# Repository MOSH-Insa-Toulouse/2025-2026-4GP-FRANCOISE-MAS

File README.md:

# Capteur de déformation en graphite - Projet 4GP

  > **Génie Physique - INSA Toulouse - Promotion 2025-2026**
  > UF « Du capteur au banc de test »

  ## Sommaire
  - [Présentation générale](#présentation-générale)
  - [1. Le capteur graphite](#1-le-capteur-graphite)
    - [1.1 Principe physique](#11-principe-physique)
    - [1.2 Objectifs et livrables](#12-objectifs-et-livrables)
    - [1.3 Matériel](#13-matériel)
  - [2. Conditionnement du signal](#2-conditionnement-du-signal)
    - [2.1 Étage transimpédance (LTSpice)](#21-étage-transimpédance-ltspice)
    - [2.2 Modèle mathématique](#22-modèle-mathématique)
  - [3. Carte électronique (shield Arduino)](#3-carte-électronique-shield-arduino)
    - [3.1 Routage sous KiCad](#31-routage-sous-kicad)
    - [3.2 Fabrication et brochage](#32-fabrication-et-brochage)
  - [4. Logiciel embarqué](#4-logiciel-embarqué)
  - [5. Application mobile](#5-application-mobile)
  - [6. Banc de caractérisation](#6-banc-de-caractérisation)
  - [7. Résultats et analyse](#7-résultats-et-analyse)
  - [8. Bilan et perspectives](#8-bilan-et-perspectives)
  - [Remerciements](#remerciements)
  - [Contacts](#contacts)

  ---

  ## Présentation générale

  Ce projet propose une chaîne de mesure complète - acquisition, traitement, affichage et
  archivage des résultats - construite autour d'un capteur de déformation **low-tech** : une simple piste
  de graphite tracée au crayon sur du papier.

  L'ensemble s'appuie sur l'article de **Lin, C.-W., Zhao, Z., Kim, J. et al. (2014)**,
  *« Pencil Drawn Strain Gauges and Chemiresistors on Paper »* (Nature). L'article de
  référence est disponible dans le dépôt.

  On cherche ic à faire un dispositif **bon marché,
  reproductible, réparable et fabricable avec des moyens d'atelier ordinaires**, tout en
  restant exploitable scientifiquement.

  ---

  ## 1. Le capteur graphite

  ### 1.1 Principe physique

  Le capteur est obtenu en frottant un crayon sur une feuille de papier (≈ 0,35 mm
  d'épaisseur). Le graphite s'accroche aux fibres et forme un réseau granulaire : le
  courant circule par les contacts entre grains et par effet tunnel entre particules
  voisines. La résistance du tracé dépend donc directement de la distance entre grains.

  Lorsque le papier est plié, cette distance évolue :

  | Sollicitation | Effet sur le réseau | Résistance |
  |---------------|---------------------|------------|
  | **Traction**  | Les grains s'écartent | **augmente** |
  | **Compression** | Les grains se rapprochent | **diminue** |

  La sensibilité dépend de plusieurs facteurs : dureté de la mine, quantité de graphite
  déposée, géométrie du tracé, humidité et température ambiantes. Différentes duretés ont
  été testées (2H, HB, B, 3B, 4B, 6B) afin de comparer leur comportement.

  ### 1.2 Objectifs et livrables

  L'objectif est de remonter à l'angle de flexion (donc à la déformation) à partir de la
  seule mesure de résistance. Le travail se décompose en cinq étapes : simulation du
  conditionnement analogique, conception du PCB, programmation du microcontrôleur,
  développement de l'application mobile et caractérisation expérimentale.

  Livrables produits :
  - un **shield Arduino** regroupant l'électronique de mesure, d'amplification et de
    communication.
  - un **code Arduino (C++)** organisé en pseudo machine à états (car nous avons essayer mais ce n'est pas réellement une machine à état).
  - une **IHM (interface human machine) en format .py** de supervision et de tracé temps réel.
  - une **datasheet** récapitulant la caractérisation du capteur.

  ### 1.3 Matériel

  **Électronique**
  - Arduino UNO Rev 3
  - Amplificateur opérationnel LTC1050
  - Potentiomètre numérique SPI MCP41010 (10 kΩ, 256 pas)
  - Écran OLED 0,96" SSD1306 (I²C)
  - Encodeur rotatif KY-040
  - Module Bluetooth HC-05
  - Passifs : résistances (2×1 kΩ, 1×10 kΩ, 2×100 kΩ) et condensateurs (2×100 nF, 1×1 µF)
  - Pour comparaison : capteur de flexion commercial (Flex Sensor) + résistance de charge 47 kΩ

  **Fabrication du capteur**
  - Papier souple, crayons de duretés variées, contacts et pinces de test Mueller

  **Logiciels**
  - LTSpice (simulation) · KiCad (PCB) · Arduino IDE (firmware)

  **Banc d'essai**
  - module imprimé en 3D à rayons de courbure étalonnés + instrumentation de mesure. Nous avons réutilisé les système imprimés les années passées pour rester dans la démarche **low-tech**

  ---

  ## 2. Conditionnement du signal

  ### 2.1 Étage transimpédance (LTSpice)

  À vide, le capteur affiche une résistance très élevée (du MΩ au GΩ selon la mine).
  Sous 5 V, le courant traversant n'est que de l'ordre du nanoampère : il faut donc un
  étage d'amplification pour ramener le signal dans la plage 0–5 V de l'ADC de l'Arduino.

  Un montage **transimpédance** autour du LTC1050 a été simulé sous LTSpice afin de valider
  le gain, étudier la réponse en fréquence et dimensionner le filtrage. Trois filtres
  passe-bas améliorent le rapport signal/bruit :

  1. **Entrée (~175 Hz)** — atténue les vibrations et tremblements mécaniques ;
  2. **Rétroaction active (~1,6 Hz)** — coupe le bruit secteur 50 Hz ;
  3. **Sortie (~1,6 kHz)** — supprime les parasites haute fréquence de l'électronique
     numérique.

  <p align="center">
    
    <br><em>Montage transimpédance autour du LTC1050 simulé sous LTSpice.</em>
  </p>

  ### 2.2 Modèle mathématique

  La tension lue par l'ADC s'écrit :

  $$V_{ADC} = \left(1 + \frac{R_3}{R_2}\right) \cdot \frac{R_1}{R_1 + R_c + R_5} \cdot V_{cc}$$

  ce qui permet au firmware de remonter à la résistance du capteur :

  $$R_c = \left(1 + \frac{R_3}{R_2}\right) \cdot R_1 \cdot \frac{V_{cc}}{V_{ADC}} - R_1 - R_5$$

  La résistance $R_2$ est pilotée dynamiquement par le potentiomètre numérique MCP41010,
  ce qui rend possible l'auto-calibration décrite plus bas.

  ---

  ## 3. Carte électronique (shield Arduino)

  ### 3.1 Routage sous KiCad

  Une fois le montage validé en simulation, le PCB a été dessiné sous KiCad pour se
  brancher directement sur l'Arduino UNO. Il a fallu créer les symboles et empreintes des
  composants absents des bibliothèques standard (Bluetooth, potentiomètre numérique…),
  puis assembler le schéma en respectant les bus **SPI** et **I²C**.

  Le placement a cherché à raccourcir les pistes analogiques et à limiter les couplages.

  <p align="center">
    
    <br><em>Architecture de la carte : rendu 3D annoté (gauche) et routage du PCB sous KiCad (droite).</em>
  </p>

  ### 3.2 Fabrication et brochage

  Le circuit a été gravé sur plaque époxy cuivrée par **photolithographie**
  (impression du masque, insolation UV, révélation, gravure au perchlorure de fer,
  perçage, soudure). *Merci à Cathy sans qui on serait sans doute encore en train de nous arracher les cheveux sur la carte.*

  Brochage retenu :

  | Composant | Rôle | Interface Arduino |
  |-----------|------|-------------------|
  | LTC1050 | Amplification transimpédance | Entrée analogique `A0` |
  | MCP41010 | Potentiomètre numérique 10 kΩ | SPI (`CS`, `MOSI: D11`, `SCK: D13`) |
  | SSD1306 | Affichage OLED | I²C (`SDA: A4`, `SCL: A5`) |
  | KY-040 | Navigation menu | Interruptions (`CLK: D2`, `DT`, `SW`) |
  | HC-05 | Liaison Bluetooth | SoftwareSerial (`RX`, `TX`) |
  | Flex Sensor | Référence commerciale | Pont diviseur (47 kΩ) |

  Des tests de continuité et de courts-circuits ont suivi l'assemblage. Une première carte
  a dû être reprise : car nous nous étions trompé avec le port qui était nécessaire aux interruptions pour le menu.

  ---

  ## 4. Logiciel embarqué

  Le firmware Arduino orchestre l'ensemble du système au moyen d'une **tentative de code de machine à états**,
  ce qui garantit un enchaînement clair des tâches :

  Fonctions principales : acquisition du signal, calcul de $R_c$, **auto-calibration** de
  la résistance à plat $R_0$ via le MCP41010 (point de repos centré à $V_{cc}/2$),
  affichage OLED, navigation par encodeur (gérée par interruptions) et transmission
  Bluetooth. Le code s'appuie sur les bibliothèques SPI, I²C et série, avec un soin
  particulier porté à la stabilité des mesures.

  ---

  ## 5. Application mobile

  Une application Android développée avec claude code dans un premier temps mais nous nous sommes rendu compte que le code était bine trop complexe pour une app qui reste assez basique. Alors nous nous sommes tournés vers une HIM python car avec nos expériences personnelles nous avions déjà été confronté à ce genre de code python pour assurer la supervision et
  l'archivage des mesures :

  - connexion au module HC-05 (sélection dans la liste, voyant d'état) ;
  - réception cadencée sur un timer de 200 ms (5 Hz) dès que des octets sont disponibles ;
  - tracé temps réel par défilement horizontal sur un `Canvas` ;
  - export des données au format `.txt` (concaténation dans une variable globale, puis
    `SaveFile`).

  L'objectif était de disposer d'une interface simple, utilisable directement pendant les
  essais.

  <p align="center">
    
    <br><em>IHM Python : connexion HC-05, tracé temps réel et export des mesures.</em>
  </p>

  ---

  ## 6. Banc de caractérisation

  Pour imposer des déformations connues, un **gabarit imprimé en 3D** a été conçu : une
  série de demi-cylindres à rayons de courbure étalonnés. Le capteur, maintenu par des
  pinces de test, y est plaqué dans deux configurations :

  - **Traction** : la piste de graphite est orientée vers l'extérieur → le maillage
    s'étire → $R_c$ augmente.
  - **Compression** : la piste est plaquée contre le cylindre → les feuillets se
    rapprochent → $R_c$ diminue.

  Chaque rayon correspond à un angle de flexion connu, ce qui permet d'étudier la
  sensibilité, la répétabilité et la réponse traction/compression pour plusieurs duretés
  de crayon.

  <p align="center">
    
    <br><em>Essai en traction : la piste de graphite est orientée vers l'extérieur.</em>
  </p>

  ---

  ## 7. Résultats et analyse

  Les mesures confirment le comportement attendu : **hausse de la résistance en traction,
  baisse en compression**, avec une forte dépendance au type de mine utilisé.

  - Les mines **tendres** (4B, 6B), riches en carbone, donnent une résistance initiale
    faible, une bonne conductivité et une réponse linéaire en compression — mais une faible
    tenue mécanique (perte de matière par frottement).
  - Les mines **plus dures** (B, 3B), plus chargées en liant, partent d'une résistance plus
    élevée et offrent un facteur de jauge supérieur, au prix d'une dérive et
    d'irrégularités caractéristiques des milieux granulaires désordonnés.

  On observe aussi que **la mesure abîme le capteur** : la résistance à plat diffère avant
  et après essai. Les acquisitions ont donc été menées en deux temps (traction puis
  compression), chacune avec sa propre *flat-band resistance*.

  <p align="center">
    
    <br><em>Courbes R = f(flexion/compression) pour les différentes mines.</em>
  </p>

  ---

  ## 8. Bilan et perspectives

  Le projet valide une **chaîne de mesure complète et connectée**, de la modélisation
  analogique jusqu'à l'application mobile, à partir de matériaux quasi gratuits.

  **Atouts** : coût matière négligeable, éco-conception, accessibilité, bonne réponse en
  traction/compression, faible consommation, capteur réparable sur place en repassant du
  graphite.

  **Limites** : répétabilité modeste (usure du film, contacts des pinces, hystérésis du
  papier) face aux jauges industrielles.

  Le capteur reste **exploitable à condition d'être calibré individuellement** : les
  valeurs absolues varient, mais le comportement relatif sous déformation est cohérent
  après étalonnage.

  Pistes d'amélioration vers un produit viable (capteurs jetables, usage pédagogique) :
  1. **électrodes fixes** imprimées plutôt que des contacts mécaniques ;
  2. **protection** du film par vernis/plastification, et vernis sur le PCB contre
     l'oxydation du cuivre.

  ---

  ## Remerciements

  Merci à l'équipe encadrante pour son accompagnement durant les phases de conception, de
  fabrication et de caractérisation : **J. Grisolia, B. Mestre, A. Biganzoli et
  C. Crouzet** — et tout particulièrement à Cathy Crouzet pour son aide en atelier PCB.

  ## Contacts

  N'hésitez pas à nous écrire pour toute question sur le projet ou les fichiers de
  fabrication :

  - **Ellande FRANCOISE** — `francoise@insa-toulouse.fr`
  - **Clément MAS** — `cmas@insa-toulouse.fr`

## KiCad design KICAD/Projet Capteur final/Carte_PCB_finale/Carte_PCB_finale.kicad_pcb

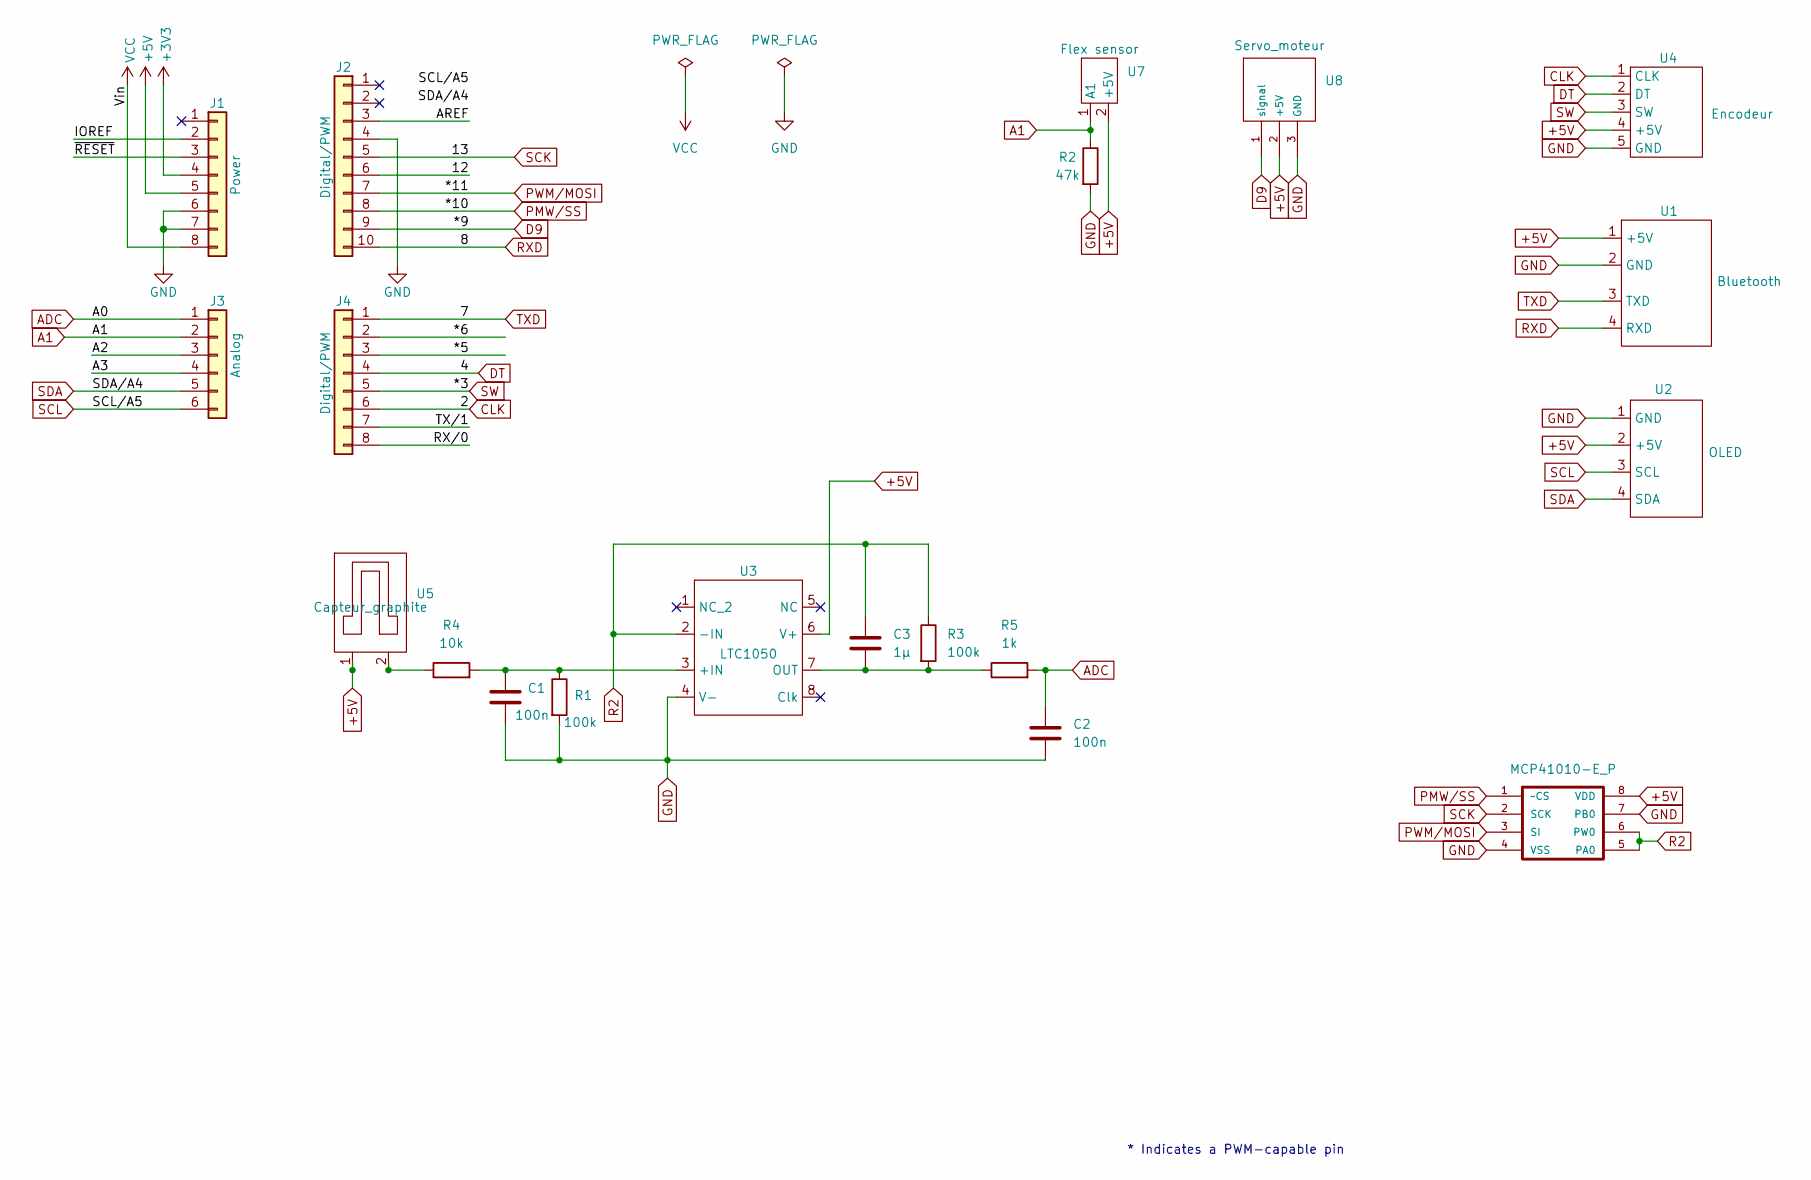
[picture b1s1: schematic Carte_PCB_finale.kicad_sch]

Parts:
C1, C2: 100n; C_Disc_D8.0mm_W2.5mm_P5.00mm
C3: 1µ; C_Rect_L7.5mm_W6.5mm_P5.00mm
J1: Power; PinSocket_1x08_P2.54mm_Vertical
J2: Digital/PWM; PinSocket_1x10_P2.54mm_Vertical
J3: Analog; PinSocket_1x06_P2.54mm_Vertical
J4: Digital/PWM; PinSocket_1x08_P2.54mm_Vertical
R1, R3: 100k; R_Axial_DIN0204_L3.6mm_D1.6mm_P5.08mm_Horizontal
R2: 47k; R_Axial_DIN0204_L3.6mm_D1.6mm_P5.08mm_Horizontal
R4: 10k; R_Axial_DIN0204_L3.6mm_D1.6mm_P5.08mm_Horizontal
R5: 1k; R_Axial_DIN0204_L3.6mm_D1.6mm_P5.08mm_Horizontal
U1: Empreinte_bluetooth
U2: empreinte_oled
U3: Empreinte_LTC1050
U4: Empreinte_encodeur
U5: Capteur_graphite
U6: MCP41010-E_P; MCP4101
U7: Flex_sensor
U8: empreinte_servo_moteur

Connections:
+3V3: J1.4
+5V: J1.5, U1.1 (+5V), U2.2 (+5V), U3.6 (V+), U4.4 (+5V), U5.1, U6.8 (VDD), U7.2 (+5V), U8.2 (+5V)
/12: J2.6
/*5: J4.3
/*6: J4.2
/A2: J3.3
/A3: J3.4
/AREF: J2.3
/IOREF: J1.2
/RX/0: J4.8
/TX/1: J4.7
/~RESET: J1.3
A1: J3.2, R2.1, U7.1 (A1)
ADC: C2.1, J3.1, R5.2
CLK: J4.6, U4.1 (CLK)
D9: J2.9, U8.1 (signal)
DT: J4.4, U4.2 (DT)
GND: C1.2, C2.2, J1.6, J1.7, J2.4, R1.2, R2.2, U1.2 (GND), U2.1 (GND), U3.4 (V-), U4.5 (GND), U6.4 (VSS), U6.7 (PB0), U8.3 (GND)
unnamed: R4.1, U5.2
unnamed: C1.1, R1.1, R4.2, U3.3 (+IN)
unnamed: C3.2, R3.2, R5.1, U3.7 (OUT)
PMW/SS: J2.8, U6.1 (~CS)
PWM/MOSI: J2.7, U6.3 (SI)
R2: C3.1, R3.1, U3.2 (-IN), U6.5 (PA0), U6.6 (PW0)
RXD: J2.10, U1.4 (RXD)
SCK: J2.5, U6.2 (SCK)
SCL: J3.6, U2.3 (SCL)
SDA: J3.5, U2.4 (SDA)
SW: J4.5, U4.3 (SW)
TXD: J4.1, U1.3 (TXD)
VCC: J1.8

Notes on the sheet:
* Indicates a PWM-capable pin

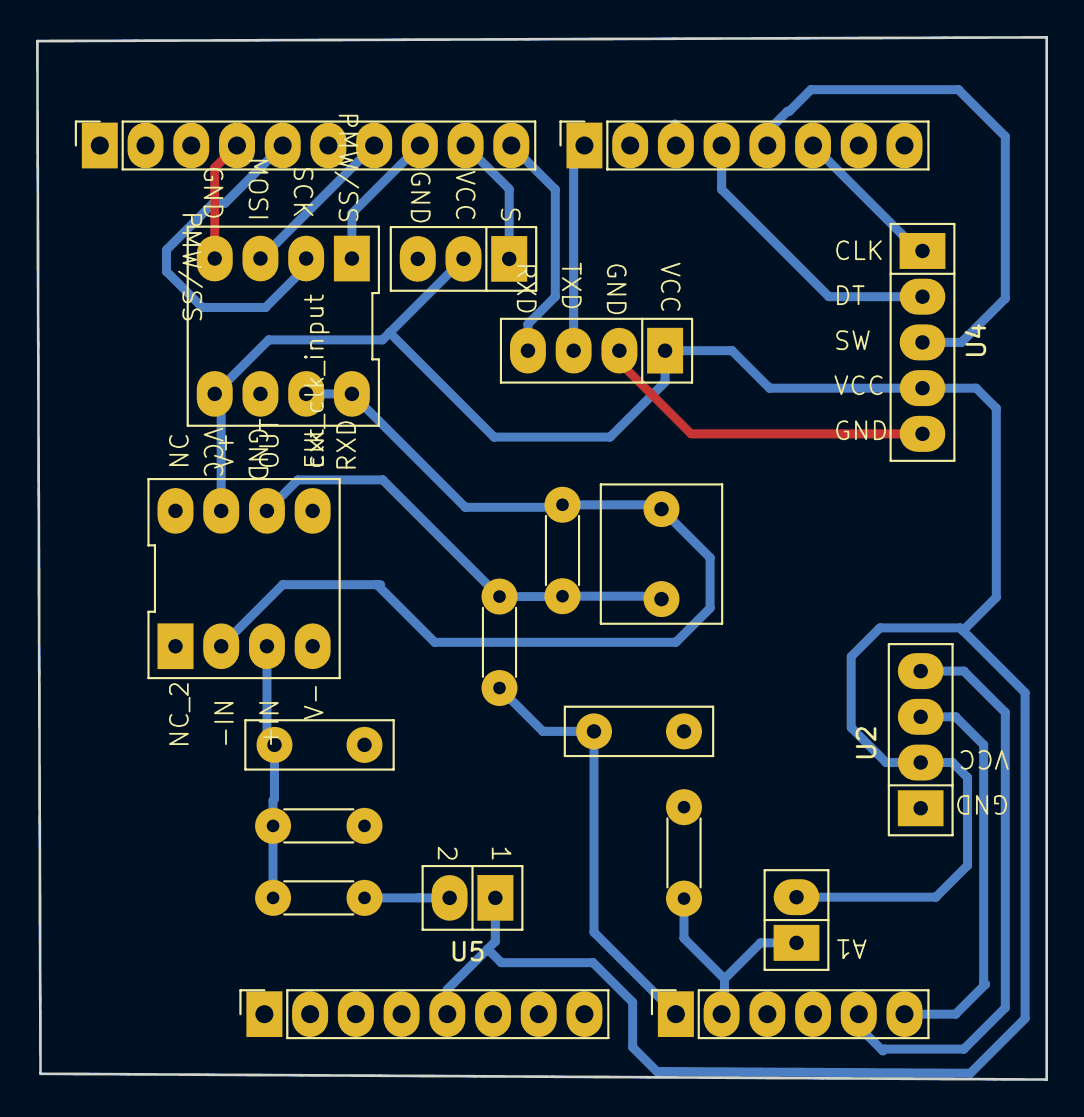
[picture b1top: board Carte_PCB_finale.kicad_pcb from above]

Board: 2 copper layers, 56.1 x 57.9 mm, 20 parts (0 on the bottom side), 19 nets.

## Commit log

2026-05-30 remplacement de licencre apache par GPL3.0
2026-05-30 version finale
